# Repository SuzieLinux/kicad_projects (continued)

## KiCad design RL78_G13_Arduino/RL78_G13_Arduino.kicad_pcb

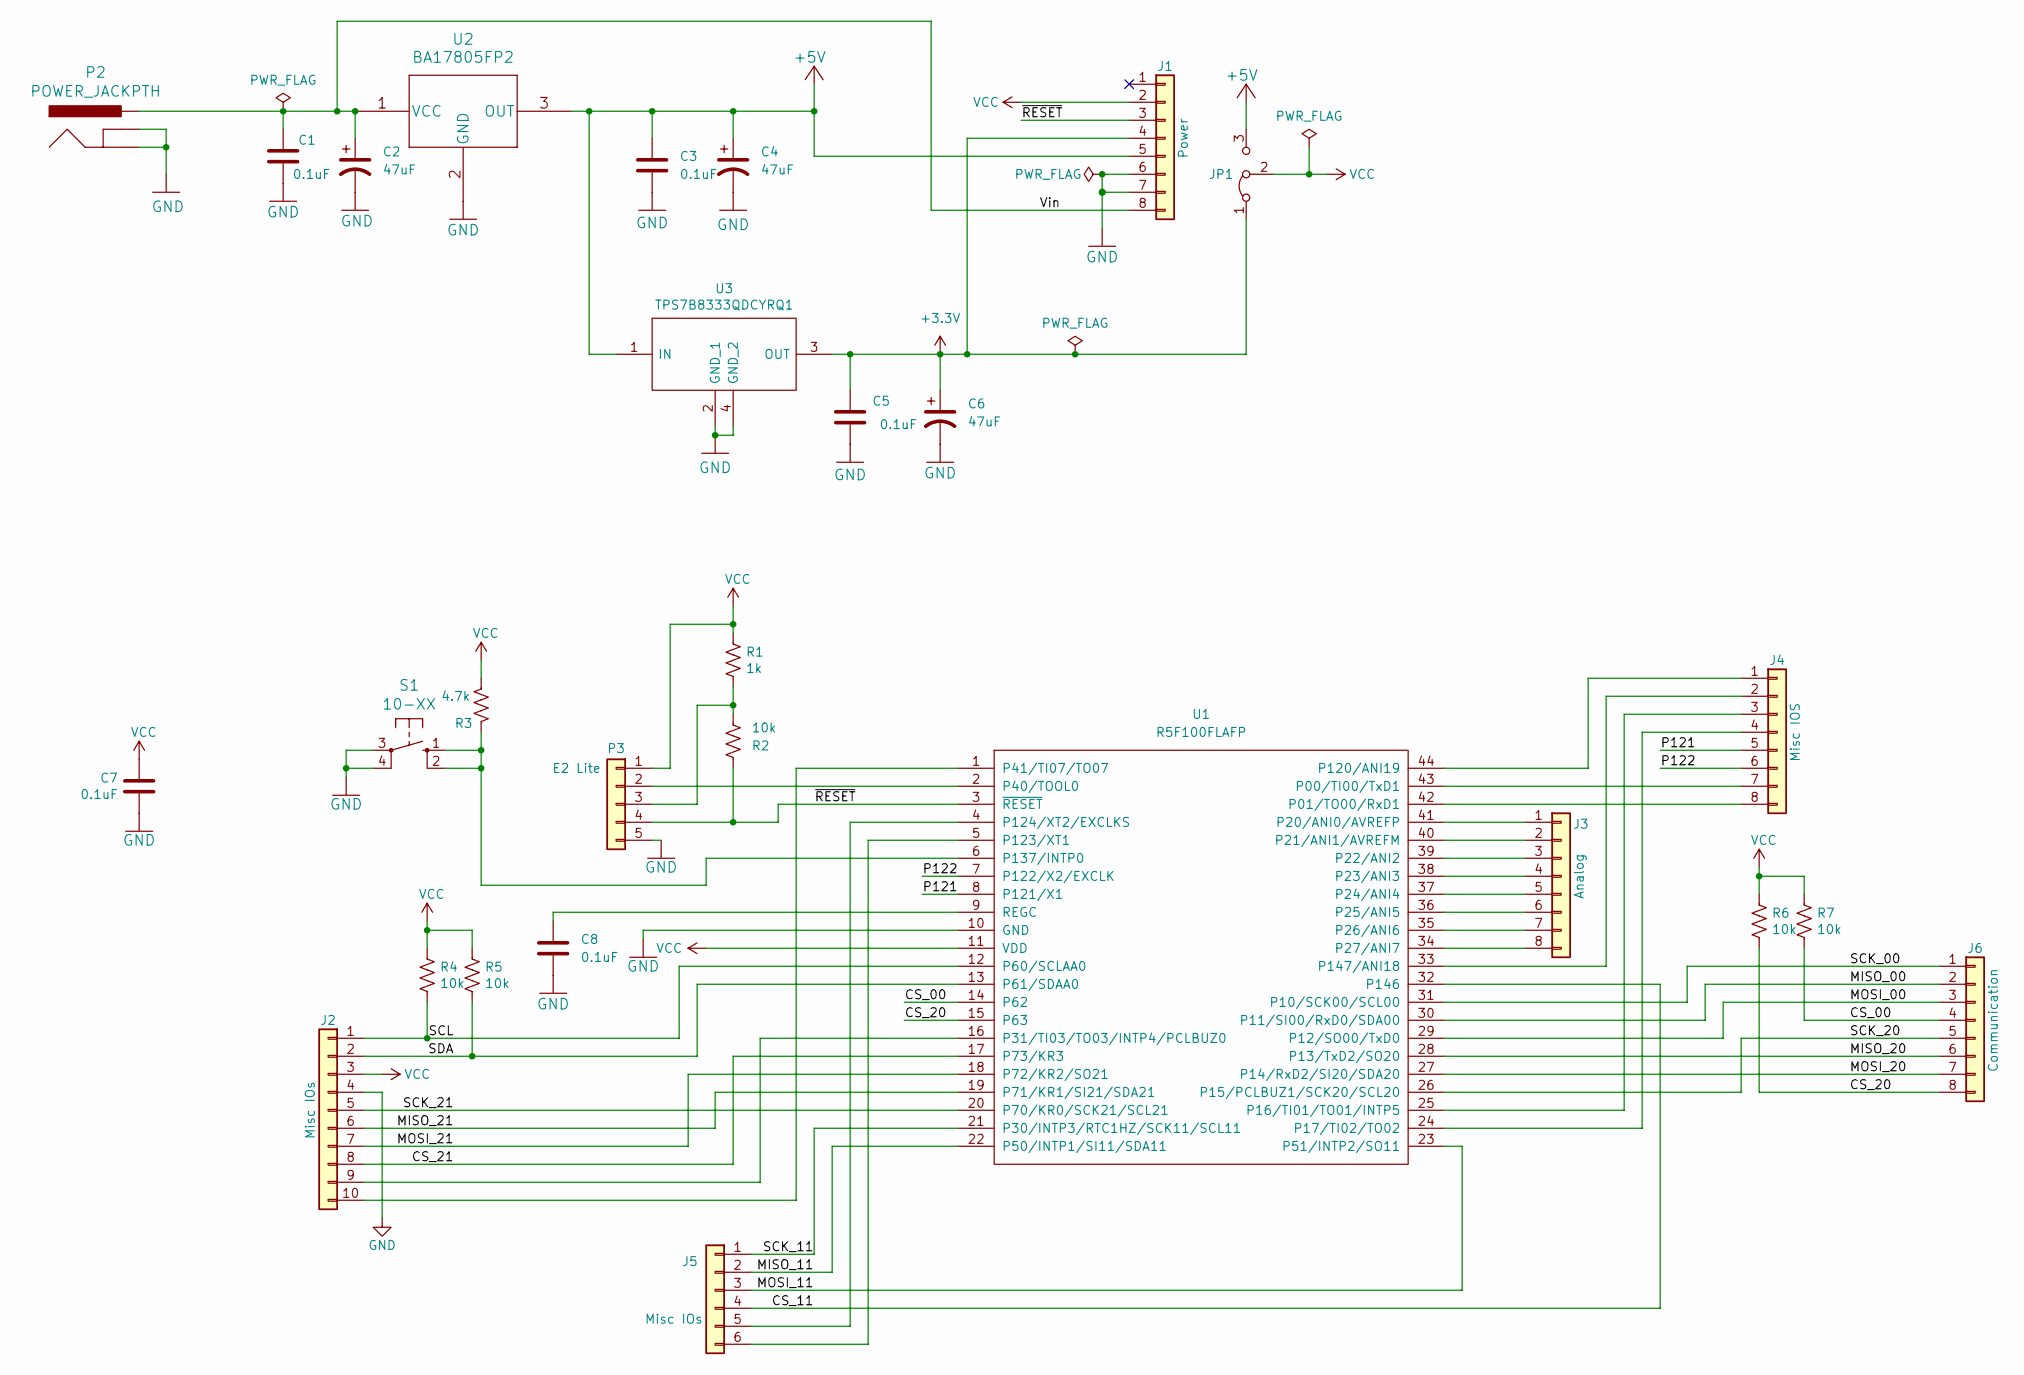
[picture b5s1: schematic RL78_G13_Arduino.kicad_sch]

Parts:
C1, C3, C5, C7, C8: 0.1uF; C_0805_2012Metric_Pad1.18x1.45mm_HandSolder
C2, C4, C6: 47uF; CP_Radial_D6.3mm_P2.50mm
J1: Power; PinSocket_1x08_P2.54mm_Vertical
J2: Misc IOs; PinSocket_1x10_P2.54mm_Vertical
J3: Analog; PinSocket_1x08_P2.54mm_Vertical
J4: Misc IOS; PinSocket_1x08_P2.54mm_Vertical
J5: Misc IOs; PinSocket_1x06_P2.54mm_Vertical
J6: Communication; PinSocket_1x08_P2.54mm_Vertical
JP1: Jumper_3_Bridged12; PinSocket_1x03_P2.54mm_Vertical
P2: POWER_JACKPTH; POWER_JACK_PTH
P3: E2 Lite; PinHeader_1x05_P2.54mm_Vertical
R1: 1k; R_0805_2012Metric
R2, R4, R5, R6, R7: 10k; R_0805_2012Metric
R3: 4.7k; R_0805_2012Metric_Pad1.20x1.40mm_HandSolder
S1: 10-XX; B3F-10XX
U1: R5F100FLAFP; LQFP-44_10x10mm_P0.8mm
U2: BA17805FP2; BA17805FP
U3: TPS7B8333QDCYRQ1; SOT230P700X180-4N

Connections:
+3.3V: C5.1, C6.1, J1.4, JP1.1 (A), U3.3 (OUT)
+5V: C3.1, C4.1, J1.5, JP1.3 (B), U2.3 (OUT), U3.1 (IN)
/CS_00: J6.4, R7.2, U1.14 (P62)
/CS_11: J5.4, U1.32 (P146)
/CS_20: J6.8, R6.2, U1.15 (P63)
/CS_21: J2.8, U1.17 (P73/KR3)
/MISO_00: J6.2, U1.30 (P11/SI00/RxD0/SDA00)
/MISO_11: J5.2, U1.22 (P50/INTP1/SI11/SDA11)
/MISO_20: J6.6, U1.28 (P13/TxD2/SO20)
/MISO_21: J2.6, U1.19 (P71/KR1/SI21/SDA21)
/MOSI_00: J6.3, U1.29 (P12/SO00/TxD0)
/MOSI_11: J5.3, U1.23 (P51/INTP2/SO11)
/MOSI_20: J6.7, U1.27 (P14/RxD2/SI20/SDA20)
/MOSI_21: J2.7, U1.18 (P72/KR2/SO21)
/P121: J4.5, U1.8 (P121/X1)
/P122: J4.6, U1.7 (P122/X2/EXCLK)
/SCK_00: J6.1, U1.31 (P10/SCK00/SCL00)
/SCK_11: J5.1, U1.21 (P30/INTP3/RTC1HZ/SCK11/SCL11)
/SCK_20: J6.5, U1.26 (P15/PCLBUZ1/SCK20/SCL20)
/SCK_21: J2.5, U1.20 (P70/KR0/SCK21/SCL21)
/SCL: J2.1, R4.2, U1.12 (P60/SCLAA0)
/SDA: J2.2, R5.2, U1.13 (P61/SDAA0)
/Vin: C1.1, C2.1, J1.8, P2.PWR, U2.1 (VCC)
/~RESET: J1.3, P3.4, R2.2, U1.3 (~RESET)
GND: C1.2, C2.2, C3.2, C4.2, C5.2, C6.2, C7.2, C8.2, J1.6, J1.7, J2.4, P2.GND, P2.GNDBREAK, P3.5, S1.3, S1.4 (P1), U1.10 (GND), U2.2 (GND), U3.2 (GND_1), U3.4 (GND_2)
unnamed: J2.9, U1.16 (P31/TI03/TO03/INTP4/PCLBUZ0)
unnamed: J2.10, U1.1 (P41/TI07/TO07)
unnamed: J3.1, U1.41 (P20/ANI0/AVREFP)
unnamed: J3.2, U1.40 (P21/ANI1/AVREFM)
unnamed: J3.3, U1.39 (P22/ANI2)
unnamed: J3.4, U1.38 (P23/ANI3)
unnamed: J3.5, U1.37 (P24/ANI4)
unnamed: J3.6, U1.36 (P25/ANI5)
unnamed: J3.7, U1.35 (P26/ANI6)
unnamed: J3.8, U1.34 (P27/ANI7)
unnamed: J4.1, U1.44 (P120/ANI19)
unnamed: J4.2, U1.33 (P147/ANI18)
unnamed: J4.3, U1.25 (P16/TI01/TO01/INTP5)
unnamed: J4.4, U1.24 (P17/TI02/TO02)
unnamed: J4.7, U1.43 (P00/TI00/TxD1)
unnamed: J4.8, U1.42 (P01/TO00/RxD1)
unnamed: J5.5, U1.4 (P124/XT2/EXCLKS)
unnamed: J5.6, U1.5 (P123/XT1)
unnamed: P3.2, U1.2 (P40/TOOL0)
unnamed: P3.3, R1.2, R2.1
unnamed: R3.1, S1.1 (S), S1.2 (S1), U1.6 (P137/INTP0)
unnamed: C8.1, U1.9 (REGC)
VCC: C7.1, J1.2, J2.3, JP1.2 (C), P3.1, R1.1, R3.2, R4.1, R5.1, R6.1, R7.1, U1.11 (VDD)

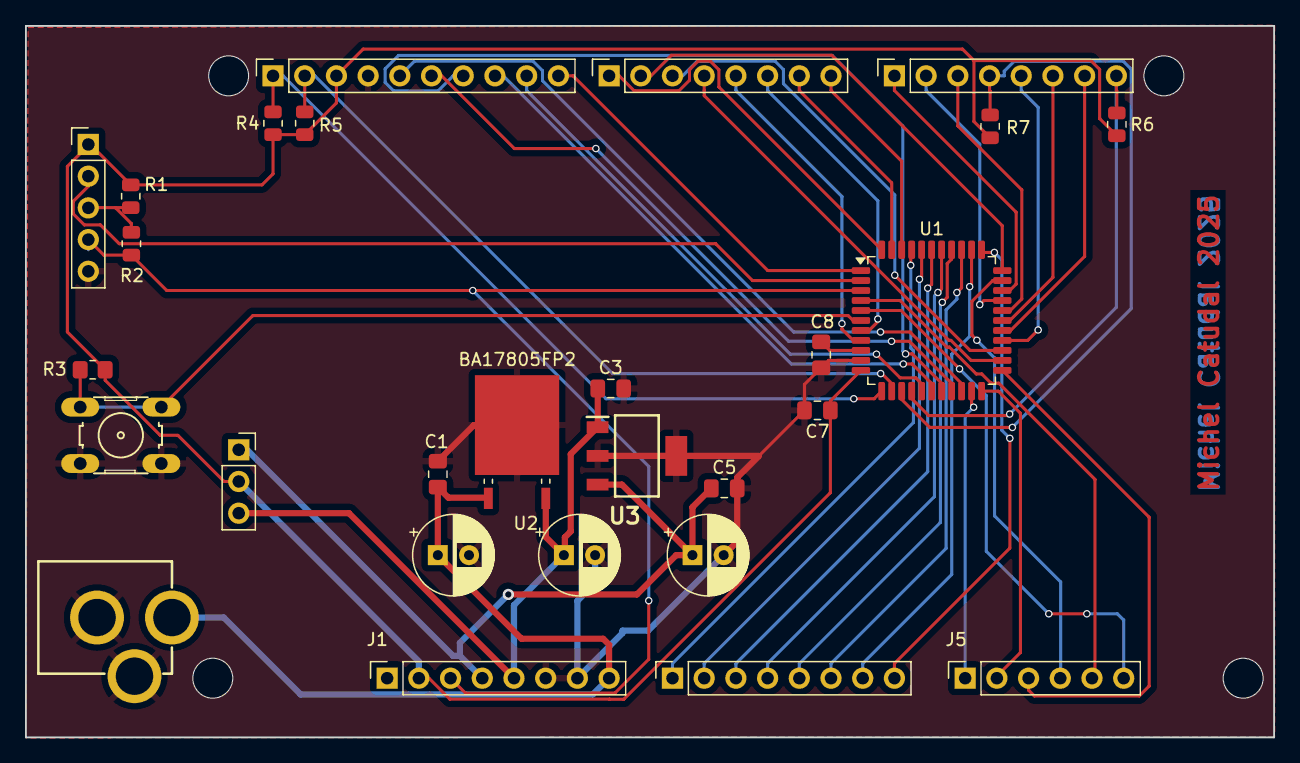
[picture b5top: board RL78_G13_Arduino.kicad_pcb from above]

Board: 2 copper layers, 100.0 x 57.0 mm, 32 parts (0 on the bottom side), 48 nets.

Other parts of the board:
MH1, MH2, MH3, MH4: MountingHole_3.2mm

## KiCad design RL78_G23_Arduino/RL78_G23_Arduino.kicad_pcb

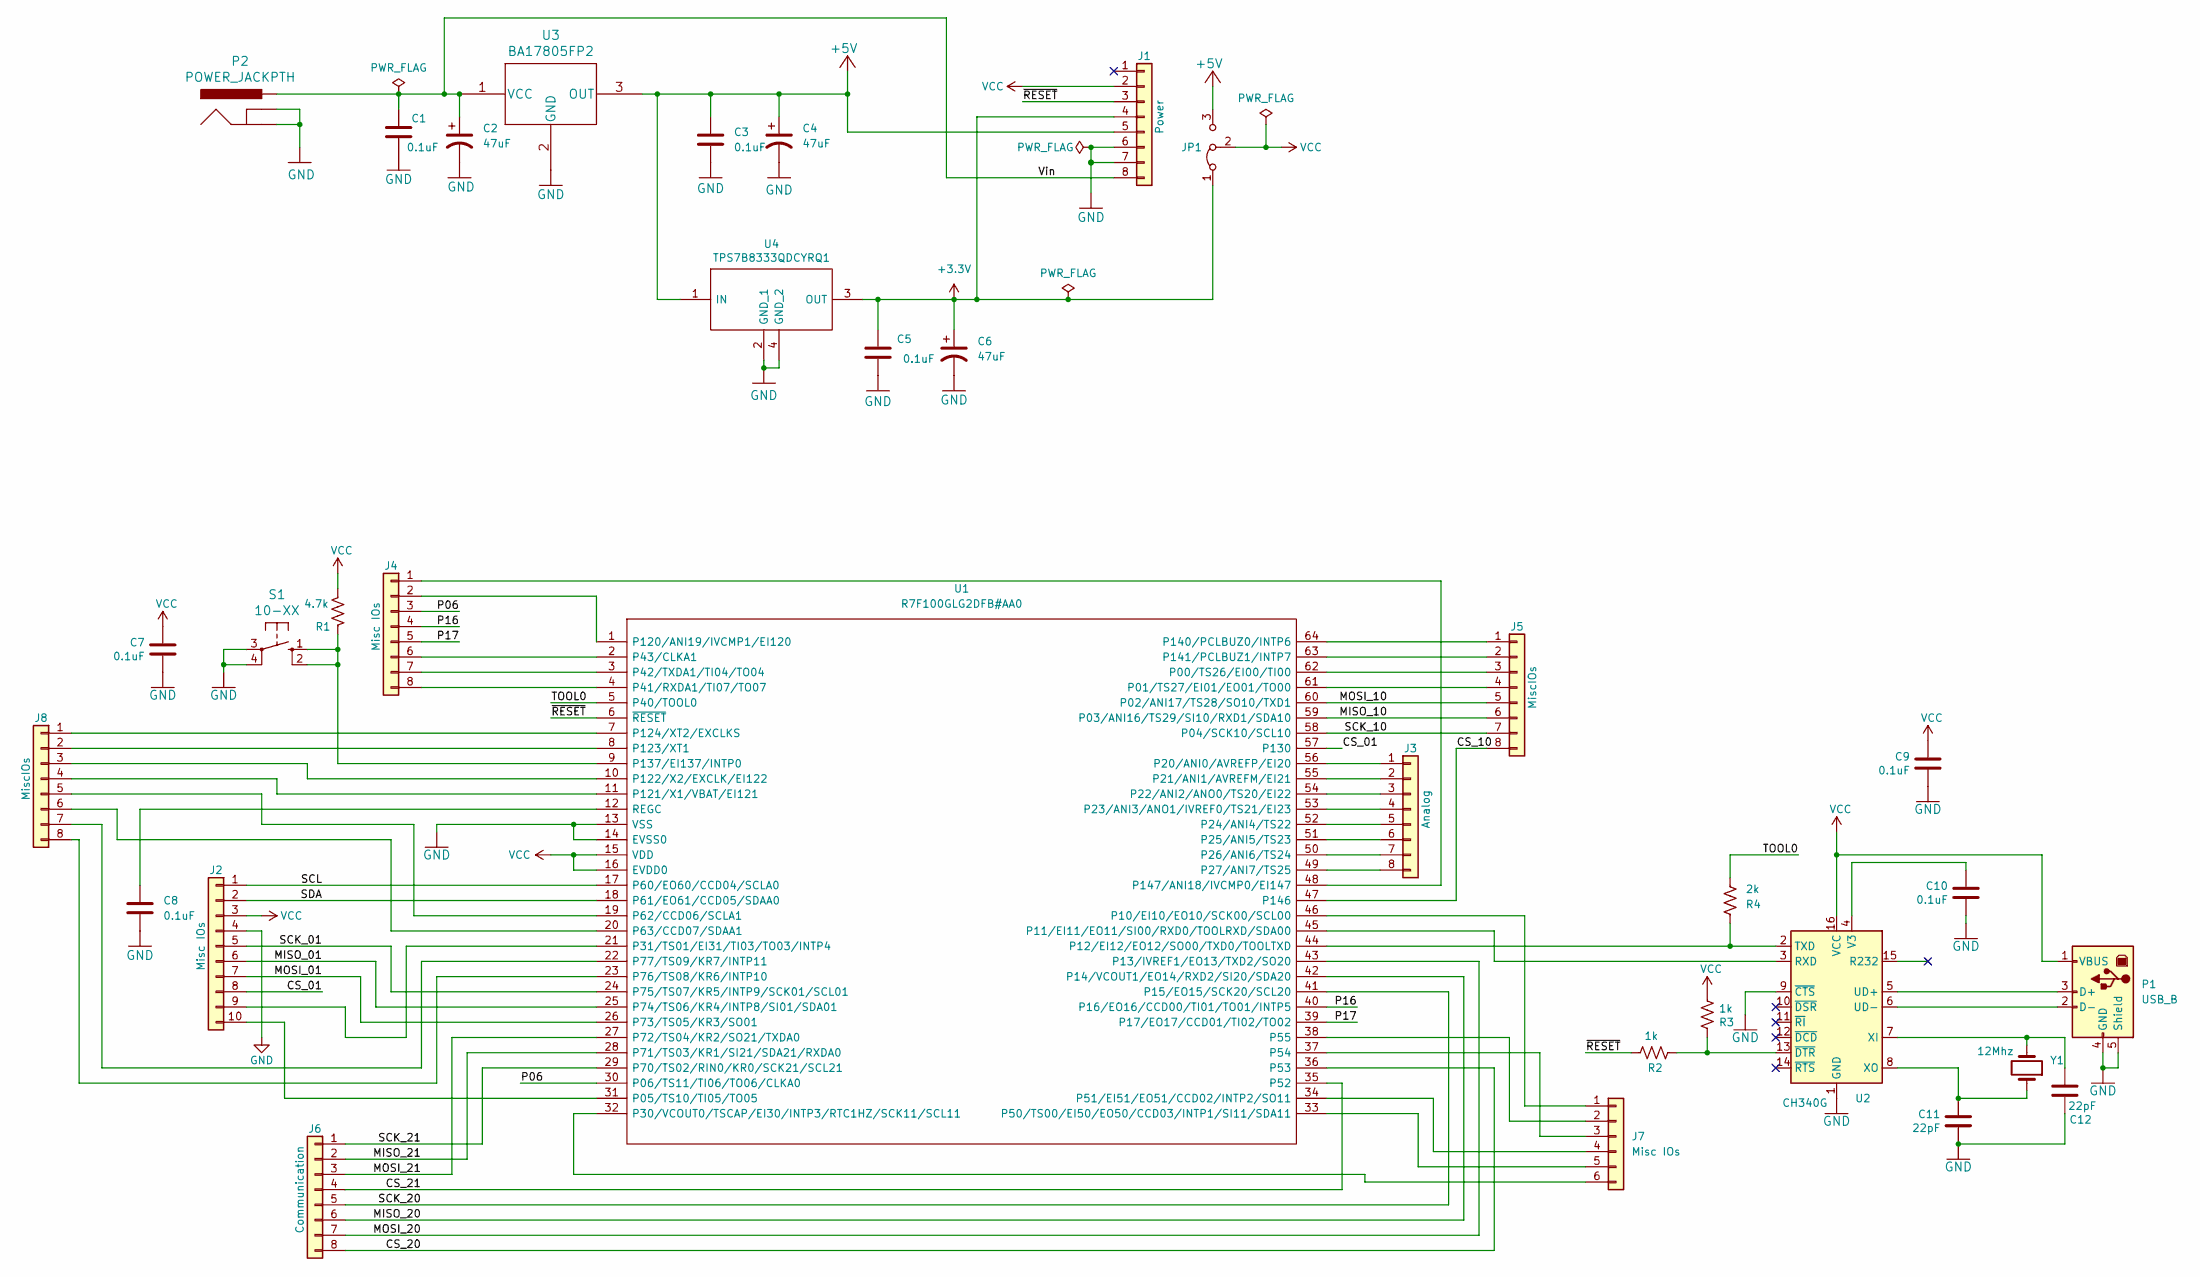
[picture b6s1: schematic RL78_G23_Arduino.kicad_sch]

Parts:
C1, C3, C5, C7, C8, C9, C10: 0.1uF; C_0805_2012Metric_Pad1.18x1.45mm_HandSolder
C2, C4, C6: 47uF; CP_Radial_D6.3mm_P2.50mm
C11, C12: 22pF; C_0805_2012Metric_Pad1.18x1.45mm_HandSolder
J1: Power; PinSocket_1x08_P2.54mm_Vertical
J2: Misc IOs; PinSocket_1x10_P2.54mm_Vertical
J3: Analog; PinSocket_1x08_P2.54mm_Vertical
J4: Misc IOs; PinSocket_1x08_P2.54mm_Vertical
J5, J8: MiscIOs; PinSocket_1x08_P2.54mm_Vertical
J6: Communication; PinSocket_1x08_P2.54mm_Vertical
J7: Misc IOs; PinSocket_1x06_P2.54mm_Vertical
JP1: Jumper_3_Bridged12; PinSocket_1x03_P2.54mm_Vertical
P1: USB_B; USB_B_OST_USB-B1HSxx_Horizontal
P2: POWER_JACKPTH; POWER_JACK_PTH
R1: 4.7k; R_0805_2012Metric_Pad1.20x1.40mm_HandSolder
R2, R3: 1k; R_0805_2012Metric
R4: 2k; R_0805_2012Metric
S1: 10-XX; B3F-10XX
U1: R7F100GLG2DFB#AA0; QFP50P1200X1200X170-64N
U2: CH340G; SOIC-16_3.9x9.9mm_P1.27mm; LCSC C14267
U3: BA17805FP2; BA17805FP
U4: TPS7B8333QDCYRQ1; SOT230P700X180-4N
Y1: 12Mhz; Crystal_HC49-4H_Vertical

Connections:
+3.3V: C5.1, C6.1, J1.4, JP1.1 (A), U4.3 (OUT)
+5V: C3.1, C4.1, J1.5, JP1.3 (B), U3.3 (OUT), U4.1 (IN)
/CS_01: J2.8, U1.57 (P130)
/CS_10: J5.8, U1.47 (P146)
/CS_20: J6.8, U1.36 (P53)
/CS_21: J6.4, U1.35 (P52)
/MISO_01: J2.6, U1.25 (P74/TS06/KR4/INTP8/SI01/SDA01)
/MISO_10: J5.6, U1.59 (P03/ANI16/TS29/SI10/RXD1/SDA10)
/MISO_20: J6.6, U1.42 (P14/VCOUT1/EO14/RXD2/SI20/SDA20)
/MISO_21: J6.2, U1.28 (P71/TS03/KR1/SI21/SDA21/RXDA0)
/MOSI_01: J2.7, U1.26 (P73/TS05/KR3/SO01)
/MOSI_10: J5.5, U1.60 (P02/ANI17/TS28/SO10/TXD1)
/MOSI_20: J6.7, U1.43 (P13/IVREF1/EO13/TXD2/SO20)
/MOSI_21: J6.3, U1.27 (P72/TS04/KR2/SO21/TXDA0)
/P06: J4.3, U1.30 (P06/TS11/TI06/TO06/CLKA0)
/P16: J4.4, U1.40 (P16/EO16/CCD00/TI01/TO01/INTP5)
/P17: J4.5, U1.39 (P17/EO17/CCD01/TI02/TO02)
/SCK_01: J2.5, U1.24 (P75/TS07/KR5/INTP9/SCK01/SCL01)
/SCK_10: J5.7, U1.58 (P04/SCK10/SCL10)
/SCK_20: J6.5, U1.41 (P15/EO15/SCK20/SCL20)
/SCK_21: J6.1, U1.29 (P70/TS02/RIN0/KR0/SCK21/SCL21)
/SCL: J2.1, U1.17 (P60/EO60/CCD04/SCLA0)
/SDA: J2.2, U1.18 (P61/EO61/CCD05/SDAA0)
/TOOL0: R4.1, U1.5 (P40/TOOL0)
/Vin: C1.1, C2.1, J1.8, P2.PWR, U3.1 (VCC)
/~RESET: J1.3, R2.1, U1.6 (~RESET)
GND: C1.2, C2.2, C3.2, C4.2, C5.2, C6.2, C7.2, C8.2, C9.2, C10.2, C11.2, C12.2, J1.6, J1.7, J2.4, P1.4 (GND), P1.5 (Shield), P2.GND, P2.GNDBREAK, S1.3, S1.4 (P1), U1.13 (VSS), U1.14 (EVSS0), U2.1 (GND), U2.9 (~CTS), U3.2 (GND), U4.2 (GND_1), U4.4 (GND_2)
unnamed: J2.9, U1.21 (P31/TS01/EI31/TI03/TO03/INTP4)
unnamed: J2.10, U1.31 (P05/TS10/TI05/TO05)
unnamed: J3.1, U1.56 (P20/ANI0/AVREFP/EI20)
unnamed: J3.2, U1.55 (P21/ANI1/AVREFM/EI21)
unnamed: J3.3, U1.54 (P22/ANI2/ANO0/TS20/EI22)
unnamed: J3.4, U1.53 (P23/ANI3/ANO1/IVREF0/TS21/EI23)
unnamed: J3.5, U1.52 (P24/ANI4/TS22)
unnamed: J3.6, U1.51 (P25/ANI5/TS23)
unnamed: J3.7, U1.50 (P26/ANI6/TS24)
unnamed: J3.8, U1.49 (P27/ANI7/TS25)
unnamed: J4.1, U1.48 (P147/ANI18/IVCMP0/EI147)
unnamed: J4.2, U1.1 (P120/ANI19/IVCMP1/EI120)
unnamed: J4.6, U1.2 (P43/CLKA1)
unnamed: J4.7, U1.3 (P42/TXDA1/TI04/TO04)
unnamed: J4.8, U1.4 (P41/RXDA1/TI07/TO07)
unnamed: J5.1, U1.64 (P140/PCLBUZ0/INTP6)
unnamed: J5.2, U1.63 (P141/PCLBUZ1/INTP7)
unnamed: J5.3, U1.62 (P00/TS26/EI00/TI00)
unnamed: J5.4, U1.61 (P01/TS27/EI01/EO01/TO00)
unnamed: J7.1, U1.46 (P10/EI10/EO10/SCK00/SCL00)
unnamed: J7.2, U1.38 (P55)
unnamed: J7.3, U1.37 (P54)
unnamed: J7.4, U1.34 (P51/EI51/EO51/CCD02/INTP2/SO11)
unnamed: J7.5, U1.33 (P50/TS00/EI50/EO50/CCD03/INTP1/SI11/SDA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)
unnamed: J7.6, U1.32 (P30/VCOUT0/TSCAP/EI30/INTP3/RTC1HZ/SCK1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)
unnamed: J8.1, U1.7 (P124/XT2/EXCLKS)
unnamed: J8.2, U1.8 (P123/XT1)
unnamed: J8.3, U1.10 (P122/X2/EXCLK/EI122)
unnamed: J8.4, U1.11 (P121/X1/VBAT/EI121)
unnamed: J8.5, U1.19 (P62/CCD06/SCLA1)
unnamed: J8.6, U1.20 (P63/CCD07/SDAA1)
unnamed: J8.7, U1.22 (P77/TS09/KR7/INTP11)
unnamed: J8.8, U1.23 (P76/TS08/KR6/INTP10)
unnamed: P1.3 (D+), U2.5 (UD+)
unnamed: P1.2 (D-), U2.6 (UD-)
unnamed: R1.1, S1.1 (S), S1.2 (S1), U1.9 (P137/EI137/INTP0)
unnamed: U1.45 (P11/EI11/EO11/SI00/RXD0/TOOLRXD/SDA00), U2.3 (RXD)
unnamed: R4.2, U1.44 (P12/EI12/EO12/SO00/TXD0/TOOLTXD), U2.2 (TXD)
unnamed: C8.1, U1.12 (REGC)
unnamed: C10.1, U2.4 (V3)
unnamed: C12.1, U2.7 (XI), Y1.2
unnamed: C11.1, U2.8 (XO), Y1.1
unnamed: R2.2, R3.1, U2.13 (~DTR)
VCC: C7.1, C9.1, J1.2, J2.3, JP1.2 (C), P1.1 (VBUS), R1.2, R3.2, U1.15 (VDD), U1.16 (EVDD0), U2.16 (VCC)

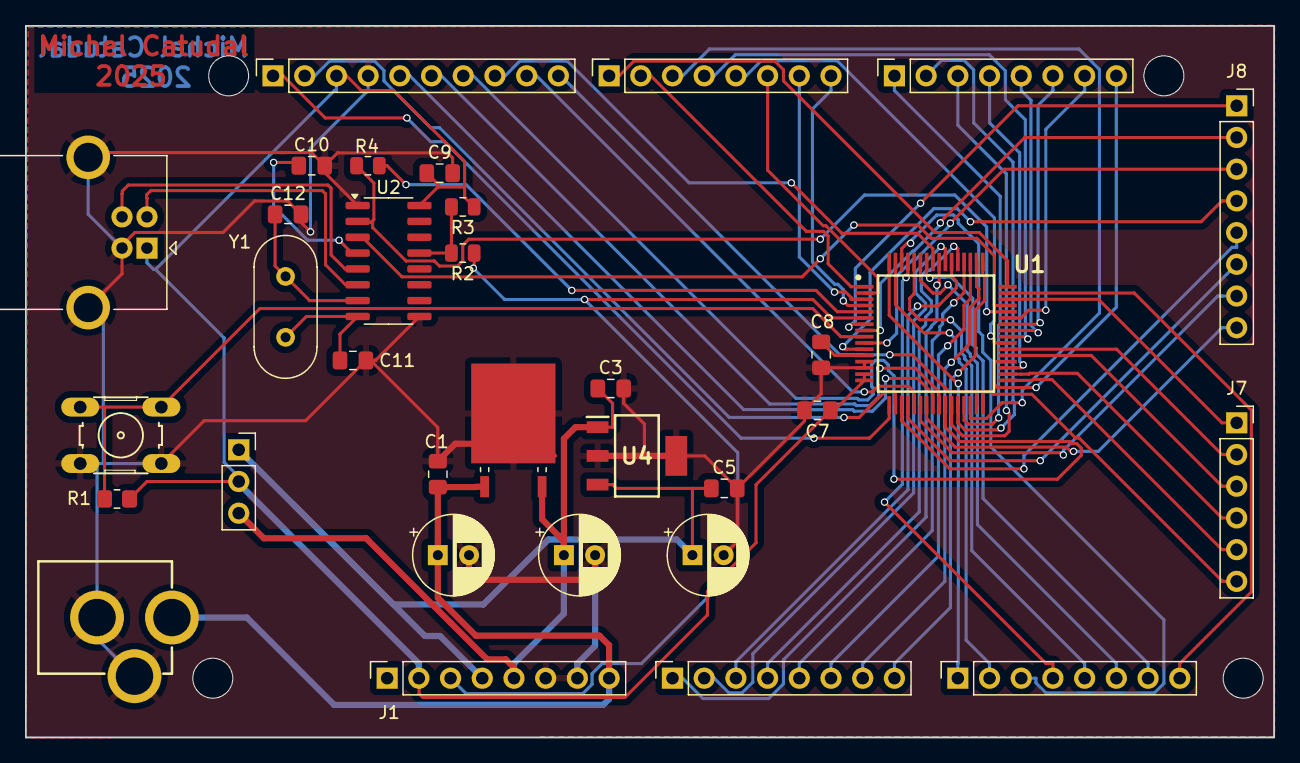
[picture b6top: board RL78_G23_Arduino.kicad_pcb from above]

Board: 2 copper layers, 100.0 x 57.0 mm, 37 parts (0 on the bottom side), 71 nets.

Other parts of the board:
MH1, MH2, MH5, MH6: MountingHole_3.2mm

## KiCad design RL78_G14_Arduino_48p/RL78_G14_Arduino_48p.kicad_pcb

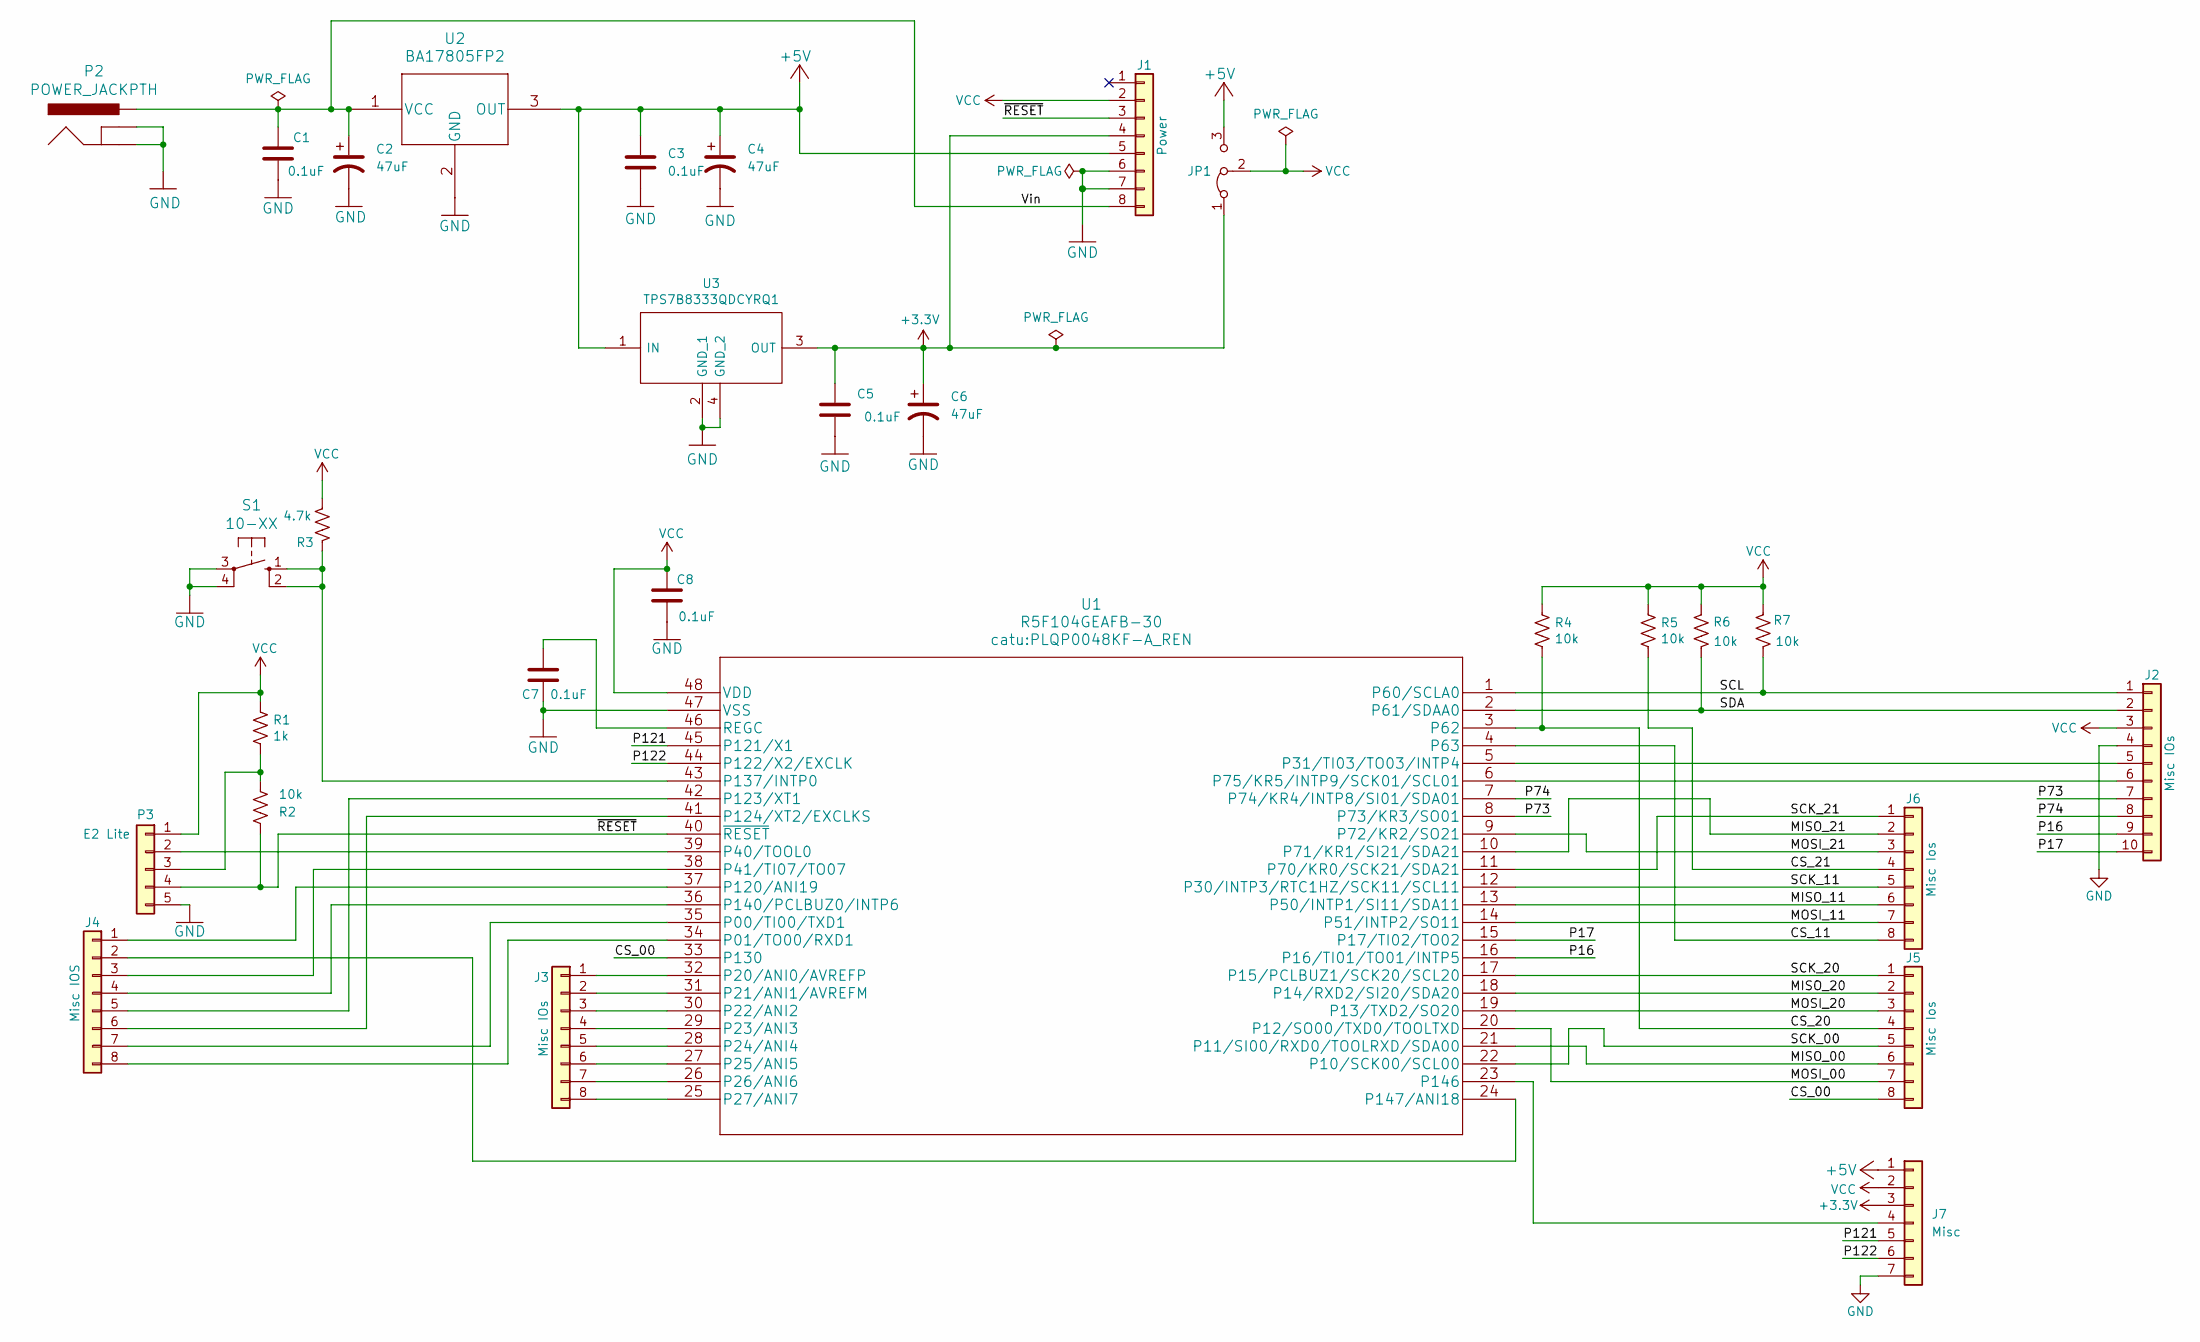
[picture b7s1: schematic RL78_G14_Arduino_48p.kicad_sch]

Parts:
C1, C3, C5, C7, C8: 0.1uF; C_0805_2012Metric_Pad1.18x1.45mm_HandSolder
C2, C4, C6: 47uF; CP_Radial_D6.3mm_P2.50mm
J1: Power; PinSocket_1x08_P2.54mm_Vertical
J2: Misc IOs; PinSocket_1x10_P2.54mm_Vertical
J3: Misc IOs; PinSocket_1x08_P2.54mm_Vertical
J4: Misc IOS; PinSocket_1x08_P2.54mm_Vertical
J5, J6: Misc Ios; PinSocket_1x08_P2.54mm_Vertical
J7: Misc; PinSocket_1x07_P2.54mm_Vertical
JP1: Jumper_3_Bridged12; PinSocket_1x03_P2.54mm_Vertical
P2: POWER_JACKPTH; POWER_JACK_PTH
P3: E2 Lite; PinHeader_1x05_P2.54mm_Vertical
R1: 1k; R_0805_2012Metric
R2, R4, R5, R6, R7: 10k; R_0805_2012Metric
R3: 4.7k; R_0805_2012Metric_Pad1.20x1.40mm_HandSolder
S1: 10-XX; B3F-10XX
U1: R5F104GEAFB-30; PLQP0048KF-A_REN
U2: BA17805FP2; BA17805FP
U3: TPS7B8333QDCYRQ1; SOT230P700X180-4N

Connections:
+3.3V: C5.1, C6.1, J1.4, J7.3, JP1.1 (A), U3.3 (OUT)
+5V: C3.1, C4.1, J1.5, J7.1, JP1.3 (B), U2.3 (OUT), U3.1 (IN)
/CS_00: J5.8, U1.33 (P130)
/CS_11: J6.8, U1.4 (P63)
/CS_20: J5.4, R4.2, U1.3 (P62)
/CS_21: J6.4, R5.2
/MISO_00: J5.6, U1.21 (P11/SI00/RXD0/TOOLRXD/SDA00)
/MISO_11: J6.6, U1.13 (P50/INTP1/SI11/SDA11)
/MISO_20: J5.2, U1.18 (P14/RXD2/SI20/SDA20)
/MISO_21: J6.2, U1.10 (P71/KR1/SI21/SDA21)
/MOSI_00: J5.7, U1.20 (P12/SO00/TXD0/TOOLTXD)
/MOSI_11: J6.7, U1.14 (P51/INTP2/SO11)
/MOSI_20: J5.3, U1.19 (P13/TXD2/SO20)
/MOSI_21: J6.3, U1.9 (P72/KR2/SO21)
/P16: J2.9, U1.16 (P16/TI01/TO01/INTP5)
/P17: J2.10, U1.15 (P17/TI02/TO02)
/P73: J2.7, U1.8 (P73/KR3/SO01)
/P74: J2.8, U1.7 (P74/KR4/INTP8/SI01/SDA01)
/P121: J7.5, U1.45 (P121/X1)
/P122: J7.6, U1.44 (P122/X2/EXCLK)
/SCK_00: J5.5, U1.22 (P10/SCK00/SCL00)
/SCK_11: J6.5, U1.12 (P30/INTP3/RTC1HZ/SCK11/SCL11)
/SCK_20: J5.1, U1.17 (P15/PCLBUZ1/SCK20/SCL20)
/SCK_21: J6.1, U1.11 (P70/KR0/SCK21/SDA21)
/SCL: J2.1, R7.2, U1.1 (P60/SCLA0)
/SDA: J2.2, R6.2, U1.2 (P61/SDAA0)
/Vin: C1.1, C2.1, J1.8, P2.PWR, U2.1 (VCC)
/~RESET: J1.3, P3.4, R2.2, U1.40 (~RESET)
GND: C1.2, C2.2, C3.2, C4.2, C5.2, C6.2, C7.2, C8.2, J1.6, J1.7, J2.4, J7.7, P2.GND, P2.GNDBREAK, P3.5, S1.3, S1.4 (P1), U1.47 (VSS), U2.2 (GND), U3.2 (GND_1), U3.4 (GND_2)
unnamed: J2.5, U1.5 (P31/TI03/TO03/INTP4)
unnamed: J2.6, U1.6 (P75/KR5/INTP9/SCK01/SCL01)
unnamed: J3.1, U1.32 (P20/ANI0/AVREFP)
unnamed: J3.2, U1.31 (P21/ANI1/AVREFM)
unnamed: J3.3, U1.30 (P22/ANI2)
unnamed: J3.4, U1.29 (P23/ANI3)
unnamed: J3.5, U1.28 (P24/ANI4)
unnamed: J3.6, U1.27 (P25/ANI5)
unnamed: J3.7, U1.26 (P26/ANI6)
unnamed: J3.8, U1.25 (P27/ANI7)
unnamed: J4.1, U1.37 (P120/ANI19)
unnamed: J4.2, U1.24 (P147/ANI18)
unnamed: J4.3, U1.38 (P41/TI07/TO07)
unnamed: J4.4, U1.36 (P140/PCLBUZ0/INTP6)
unnamed: J4.5, U1.42 (P123/XT1)
unnamed: J4.6, U1.41 (P124/XT2/EXCLKS)
unnamed: J4.7, U1.35 (P00/TI00/TXD1)
unnamed: J4.8, U1.34 (P01/TO00/RXD1)
unnamed: J7.4, U1.23 (P146)
unnamed: P3.2, U1.39 (P40/TOOL0)
unnamed: P3.3, R1.2, R2.1
unnamed: R3.1, S1.1 (S), S1.2 (S1), U1.43 (P137/INTP0)
unnamed: C7.1, U1.46 (REGC)
VCC: C8.1, J1.2, J2.3, J7.2, JP1.2 (C), P3.1, R1.1, R3.2, R4.1, R5.1, R6.1, R7.1, U1.48 (VDD)

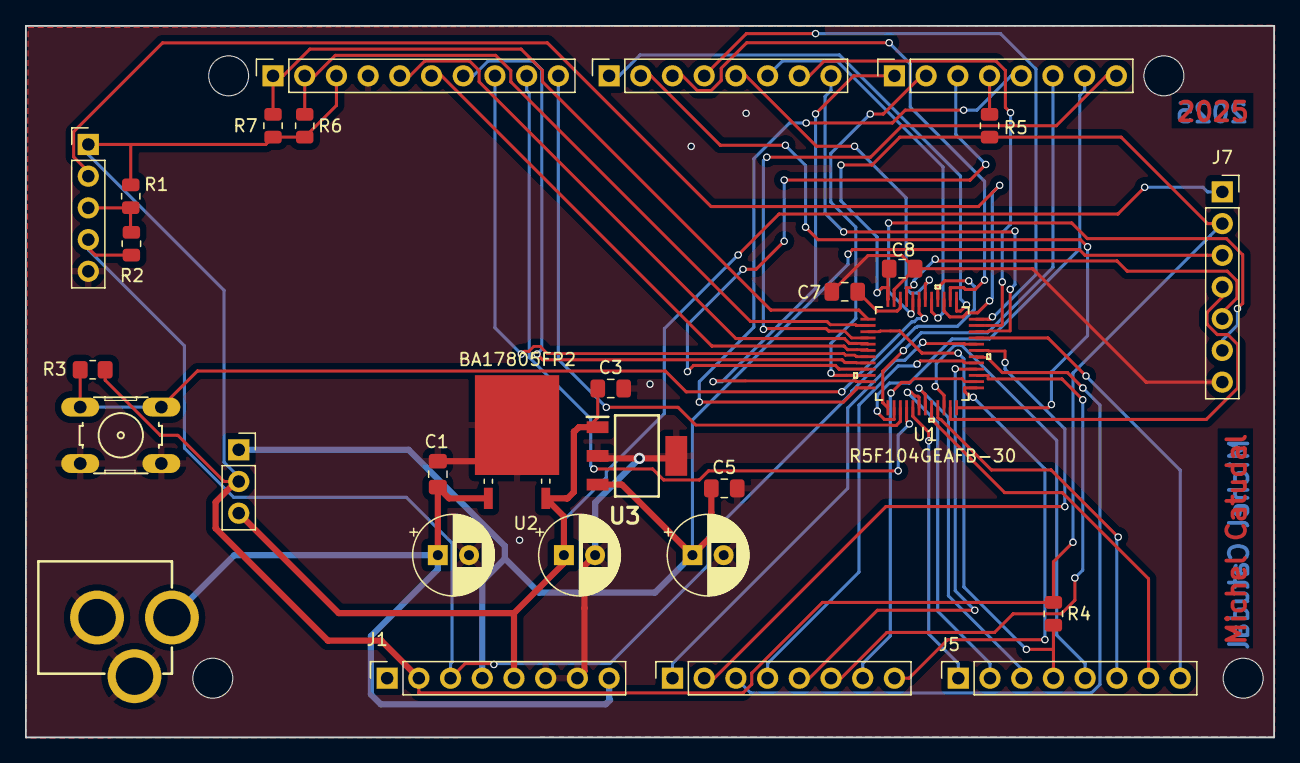
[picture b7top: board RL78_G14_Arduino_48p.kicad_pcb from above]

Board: 2 copper layers, 100.0 x 57.0 mm, 33 parts (0 on the bottom side), 53 nets.

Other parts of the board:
MH1, MH2, MH3, MH4: MountingHole_3.2mm

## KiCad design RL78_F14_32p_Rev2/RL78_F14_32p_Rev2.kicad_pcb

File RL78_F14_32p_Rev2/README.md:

This board uses a RL78 F14 
The configuration for F14 is only supported by applilet3
Take note that the software for the on board CAN is not supported by
applilet3

Once I have this board working I will publish my source code

The board runs at 5V.
The LCD is Chanruida 1.8 inch TFT LCD 128 × 160 color screen 
ST7735 SPI display LCD module with SD card slot arduino display display lcd

The ethernet adapter is a small board called W5500 SPI to LAN ethernet
network module

The keypad is a 4x5 keypad

The debugger used is E2 Lite. I have an adapter so you can connect the
debugger to it.

Feel free to use this board but if you are going to make money with it be
nice enough to make a donation on my website.

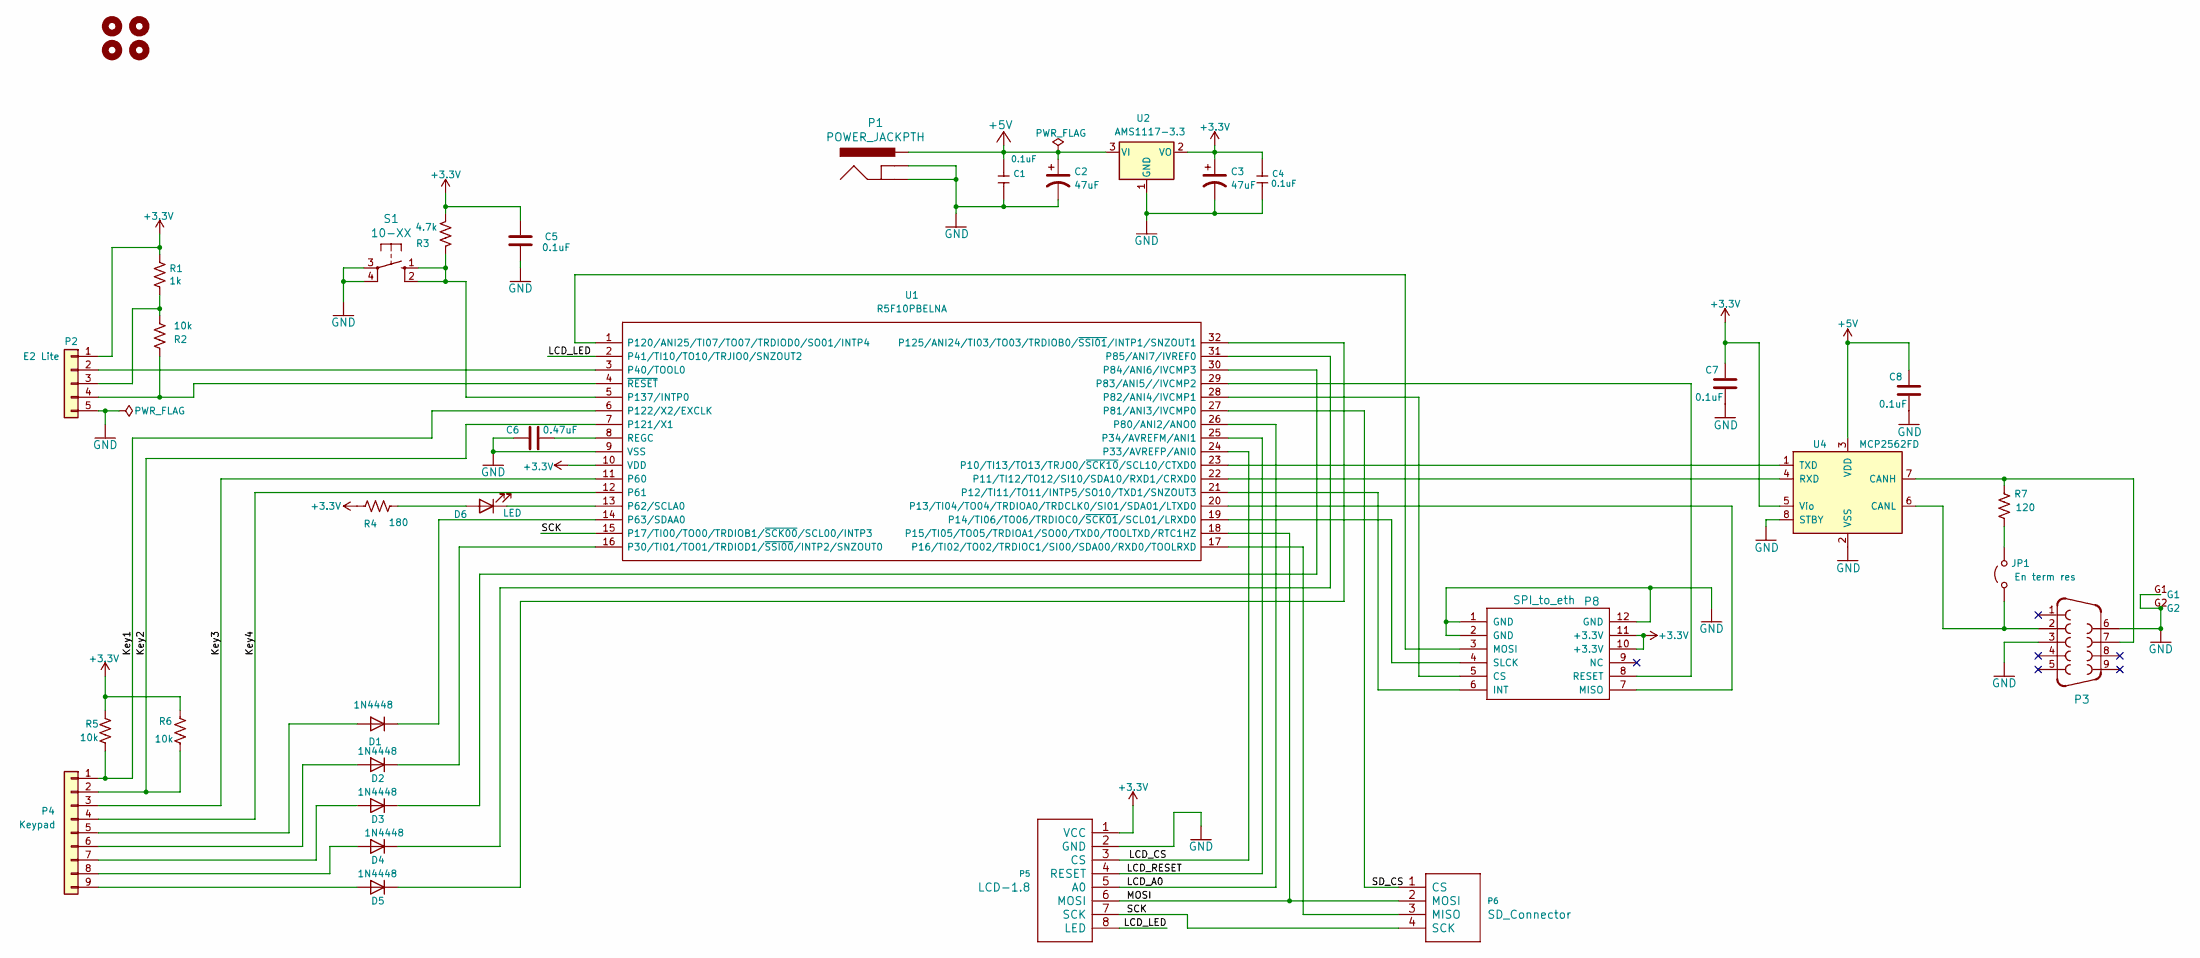
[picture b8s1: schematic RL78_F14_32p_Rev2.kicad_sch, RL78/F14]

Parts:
C1, C4: 0.1uF; C_0805_2012Metric_Pad1.18x1.45mm_HandSolder; MPN CC0603KRX7R9BB104; LCSC C14663
C2, C3: 47uF; CP_Radial_D6.3mm_P2.50mm
C5, C7, C8: 0.1uF; C_0805_2012Metric_Pad1.18x1.45mm_HandSolder
C6: 0.47uF; C_0805_2012Metric_Pad1.18x1.45mm_HandSolder
D1, D2, D3, D4, D5: 1N4448; D_DO-35_SOD27_P7.62mm_Horizontal
D6: LED; LED_D5.0mm
H1, H2, H3, H4: MountingHole; MountingHole_2.7mm_M2.5_DIN965_Pad
JP1: En term res; PinHeader_1x02_P2.54mm_Vertical
P1: POWER_JACKPTH; POWER_JACK_PTH
P2: E2 Lite; PinHeader_1x05_P2.54mm_Vertical
P3: F09HP
P4: Keypad; PinHeader_1x09_P2.54mm_Vertical
P5: LCD-1.8; PinHeader_1x08_P2.54mm_Vertical
P6: SD_Connector; PinHeader_1x04_P2.54mm_Vertical
P8: SPI_to_eth
R1: 1k; R_0805_2012Metric
R2, R5, R6: 10k; R_0805_2012Metric
R3: 4.7k; R_0805_2012Metric_Pad1.20x1.40mm_HandSolder
R4: 180; R_0805_2012Metric
R7: 120; R_2512_6332Metric_Pad1.40x3.35mm_HandSolder
S1: 10-XX; B3F-10XX
U1: R5F10PBELNA; QFN-32-1EP_5x5mm_P0.5mm_EP3.65x3.65mm; Manufacturer_Part_Number R5F10BELNA#5
U2: AMS1117-3.3; SOT-223-3_TabPin2; LCSC C6186
U4: MCP2562FD; DIP-8_W7.62mm

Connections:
+3.3V: C3.1, C4.1, C5.1, C7.1, P2.1, P5.1 (VCC), P8.10 (+3.3V), P8.11 (+3.3V), R1.1, R3.2, R4.1, R5.1, R6.1, U1.10 (VDD), U2.2 (VO), U4.5 (Vio)
+5V: C1.1, C2.1, C8.1, P1.PWR, U2.3 (VI), U4.3 (VDD)
/Key1: P4.1, R5.2, U1.6 (P122/X2/EXCLK)
/Key2: P4.2, R6.2, U1.7 (P121/X1)
/Key3: P4.3, U1.11 (P60)
/Key4: P4.4, U1.12 (P61)
/LCD_A0: P5.5 (A0), U1.26 (P80/ANI2/ANO0)
/LCD_CS: P5.3 (CS), U1.24 (P33/AVREFP/ANI0)
/LCD_LED: P5.8 (LED), U1.2 (P41/TI10/TO10/TRJIO0/SNZOUT2)
/LCD_RESET: P5.4 (RESET), U1.25 (P34/AVREFM/ANI1)
/MOSI: P5.6 (MOSI), P6.2 (MOSI), U1.18 (P15/TI05/TO05/TRDIOA1/SO00/TXD0/TOOLTXD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)
/SCK: P5.7 (SCK), P6.4 (SCK), U1.15 (P17/TI00/TO00/TRDIOB1/~SCK00/SCL00/INTP3)
/SD_CS: P6.1 (CS), U1.27 (P81/ANI3/IVCMP0)
GND: C1.2, C2.2, C3.2, C4.2, C5.2, C6.2, C7.2, C8.2, P1.GND, P1.GNDBREAK, P2.5, P3.3, P3.6, P3.G1, P3.G2, P5.2 (GND), P8.1 (GND), P8.2 (GND), P8.12 (GND), S1.3, S1.4 (P1), U1.9 (VSS), U2.1 (GND), U4.2 (VSS), U4.8 (STBY)
unnamed: D1.2 (A), P4.5
unnamed: D1.1 (K), U1.14 (P63/SDAA0)
unnamed: D2.2 (A), P4.6
unnamed: D2.1 (K), U1.16 (P30/TI01/TO01/TRDIOD1/~SSI00/INTP2/SNZO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)
unnamed: D3.2 (A), P4.7
unnamed: D3.1 (K), U1.30 (P84/ANI6/IVCMP3)
unnamed: D4.2 (A), P4.8
unnamed: D4.1 (K), U1.31 (P85/ANI7/IVREF0)
unnamed: D5.2 (A), P4.9
unnamed: D5.1 (K), U1.32 (P125/ANI24/TI03/TO03/TRDIOB0/~SSI01/INT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)
unnamed: D6.2 (A), R4.2
unnamed: D6.1 (K), U1.13 (P62/SCLA0)
unnamed: JP1.1 (A), P3.2, U4.6 (CANL)
unnamed: JP1.2 (B), R7.2
unnamed: P2.2, U1.3 (P40/TOOL0)
unnamed: P2.3, R1.2, R2.1
unnamed: P2.4, R2.2, U1.4 (~RESET)
unnamed: P6.3 (MISO), U1.17 (P16/TI02/TO02/TRDIOC1/SI00/SDA00/RXD0/T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)
unnamed: P8.5 (CS), U1.28 (P82/ANI4/IVCMP1)
unnamed: P8.6 (INT), U1.21 (P12/TI11/TO11/INTP5/SO10/TXD1/SNZOUT3)
unnamed: P8.7 (MISO), U1.20 (P13/TI04/TO04/TRDIOA0/TRDCLK0/SI01/SDA0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)
unnamed: P8.3 (MOSI), U1.1 (P120/ANI25/TI07/TO07/TRDIOD0/SO01/INTP4)
unnamed: P8.8 (RESET), U1.29 (P83/ANI5//IVCMP2)
unnamed: P8.4 (SLCK), U1.19 (P14/TI06/TO06/TRDIOC0/~SCK01/SCL01/LRXD0)
unnamed: R3.1, S1.1 (S), S1.2 (S1), U1.5 (P137/INTP0)
unnamed: U1.23 (P10/TI13/TO13/TRJO0/~SCK10/SCL10/CTXD0), U4.1 (TXD)
unnamed: U1.22 (P11/TI12/TO12/SI10/SDA10/RXD1/CRXD0), U4.4 (RXD)
unnamed: C6.1, U1.8 (REGC)
unnamed: P3.7, R7.1, U4.7 (CANH)
